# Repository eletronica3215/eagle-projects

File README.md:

# Eagle
Projetos para consolidar os conhecimentos em eletrônica, assim como, aprofundar os conhecimentos na simulação do software.

Versão utilizada: 9.5.2

# Projetos

## Circuitos Digitais
* Decodificador para display de 7 segmentos de 2 bits
	
## Circuitos analógicos

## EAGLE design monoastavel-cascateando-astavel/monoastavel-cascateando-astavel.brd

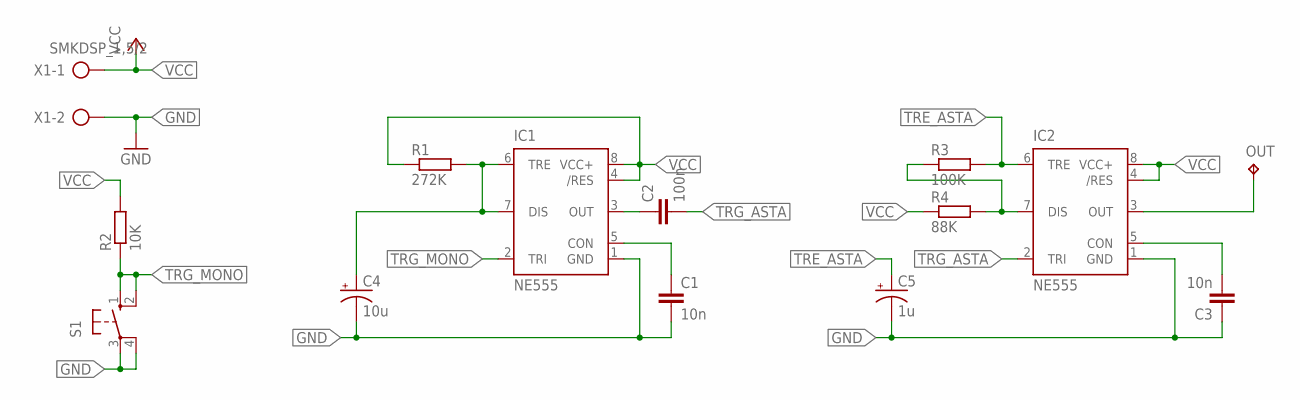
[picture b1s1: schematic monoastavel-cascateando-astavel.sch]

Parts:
C1, C3: 10n; C2.5-2
C2: 100n; C2.5-2
C4: 10u; TAP5-60
C5: 1u; TAP5-60
IC1, IC2: NE555; DIL-08
OUT: TPPAD1-13; P1-13
R1: 272K; 0207/10
R2: 10K; 0207/10
R3: 100K; 0207/10
R4: 88K; 0207/10
S1: 10-XX; B3F-10XX
X1: SMKDSP_1,5/2

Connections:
GND: C1.2, C3.1, C4.-, C5.-, IC1.1 (GND), IC2.1 (GND), S1.3, S1.4 (P1), X1.2
unnamed: IC2.7 (DIS), R3.1, R4.2
unnamed: C3.2, IC2.5 (CON)
unnamed: IC2.3 (OUT), OUT.TP
unnamed: C1.1, IC1.5 (CON)
unnamed: C2.1, IC1.3 (OUT)
unnamed: C4.+, IC1.6 (TRE), IC1.7 (DIS), R1.2
TRE_ASTA: C5.+, IC2.6 (TRE), R3.2
TRG_ASTA: C2.2, IC2.2 (TRI)
TRG_MONO: IC1.2 (TRI), R2.1, S1.1 (S), S1.2 (S1)
VCC: IC1.4 (/RES), IC1.8 (VCC+), IC2.4 (/RES), IC2.8 (VCC+), R1.1, R2.2, R4.1, X1.1

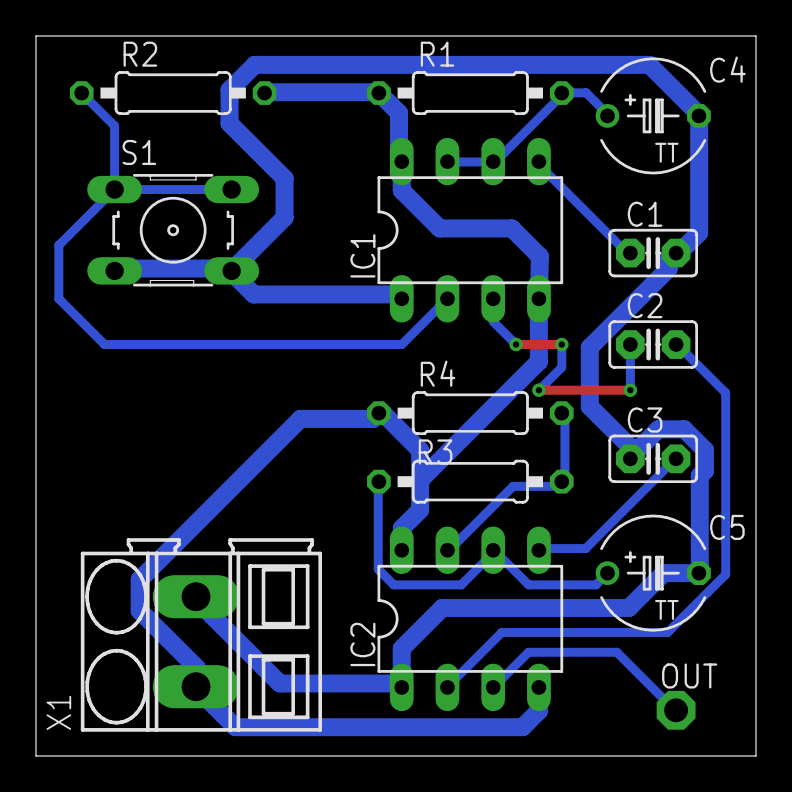
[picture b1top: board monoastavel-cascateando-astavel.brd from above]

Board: 2 copper layers, 40.0 x 40.0 mm, 14 parts (0 on the bottom side), 11 nets.

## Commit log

2020-11-25 Criado o README.md
2020-11-25 README.md atualizado
2020-11-25 Criado o projeto do Decodificador para display de 7 segmentos de 2 bits
2020-11-26 Criado o esquemático do projeto e elaborada a simulação
2021-01-08 Projeto 7 segmentos modificado
2021-01-08 Projeto para revisar o funcionamento das portas lógicas
2021-01-08 Projeto de um monoastável de 3s cascateando um astável de 5hz
